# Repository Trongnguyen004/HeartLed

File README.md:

### HeartLed chưa được hoàn thiện 100% vì còn vướng về khâu tiết kiệm năng lượng vì sử dụng các pin CR2032, LIR2032, các loại pin có kích thước nhỏ mới phù hợp để làm 1 chiếc móc khóa.
### Vì giới hạn về mặt kiến thức lập trình nên hiện tại chưa thể can thiệp sâu vào các chế độ ngủ của chip. Vậy nên vấn đề trên sẽ được cải thiện dần trong thời gian tới.

### #Design 
<p align="center">
  <table>
    <tr>
      <td>
        
      </td>
      <td>
        
      </td>
      <td>
        
      </td>
    </tr>
  </table>
</p>

### #3D View
<p align="center">
  <table>
    <tr>
      <td>
        
      </td>
      <td>
        
      </td>
      <td>
        
      </td>
    </tr>
  </table>
</p>

### #Thành phẩm 
<p align="center">
  <table>
    <tr>
      <td>
        
      </td>
      <td>
        
      </td>
      <td>
        
      </td>
    </tr>
  </table>
</p>

### #Video
https://github.com/Trongnguyen004/HeartLed/assets/137270832/59e95ee1-c4d1-4318-9db8-90237cea7051

https://github.com/Trongnguyen004/HeartLed/assets/137270832/5ad59888-f046-4cde-adbe-0e13fbfc24e3

https://github.com/Trongnguyen004/HeartLed/assets/137270832/b6c706a9-fdab-4b93-9083-bb33e0925c82

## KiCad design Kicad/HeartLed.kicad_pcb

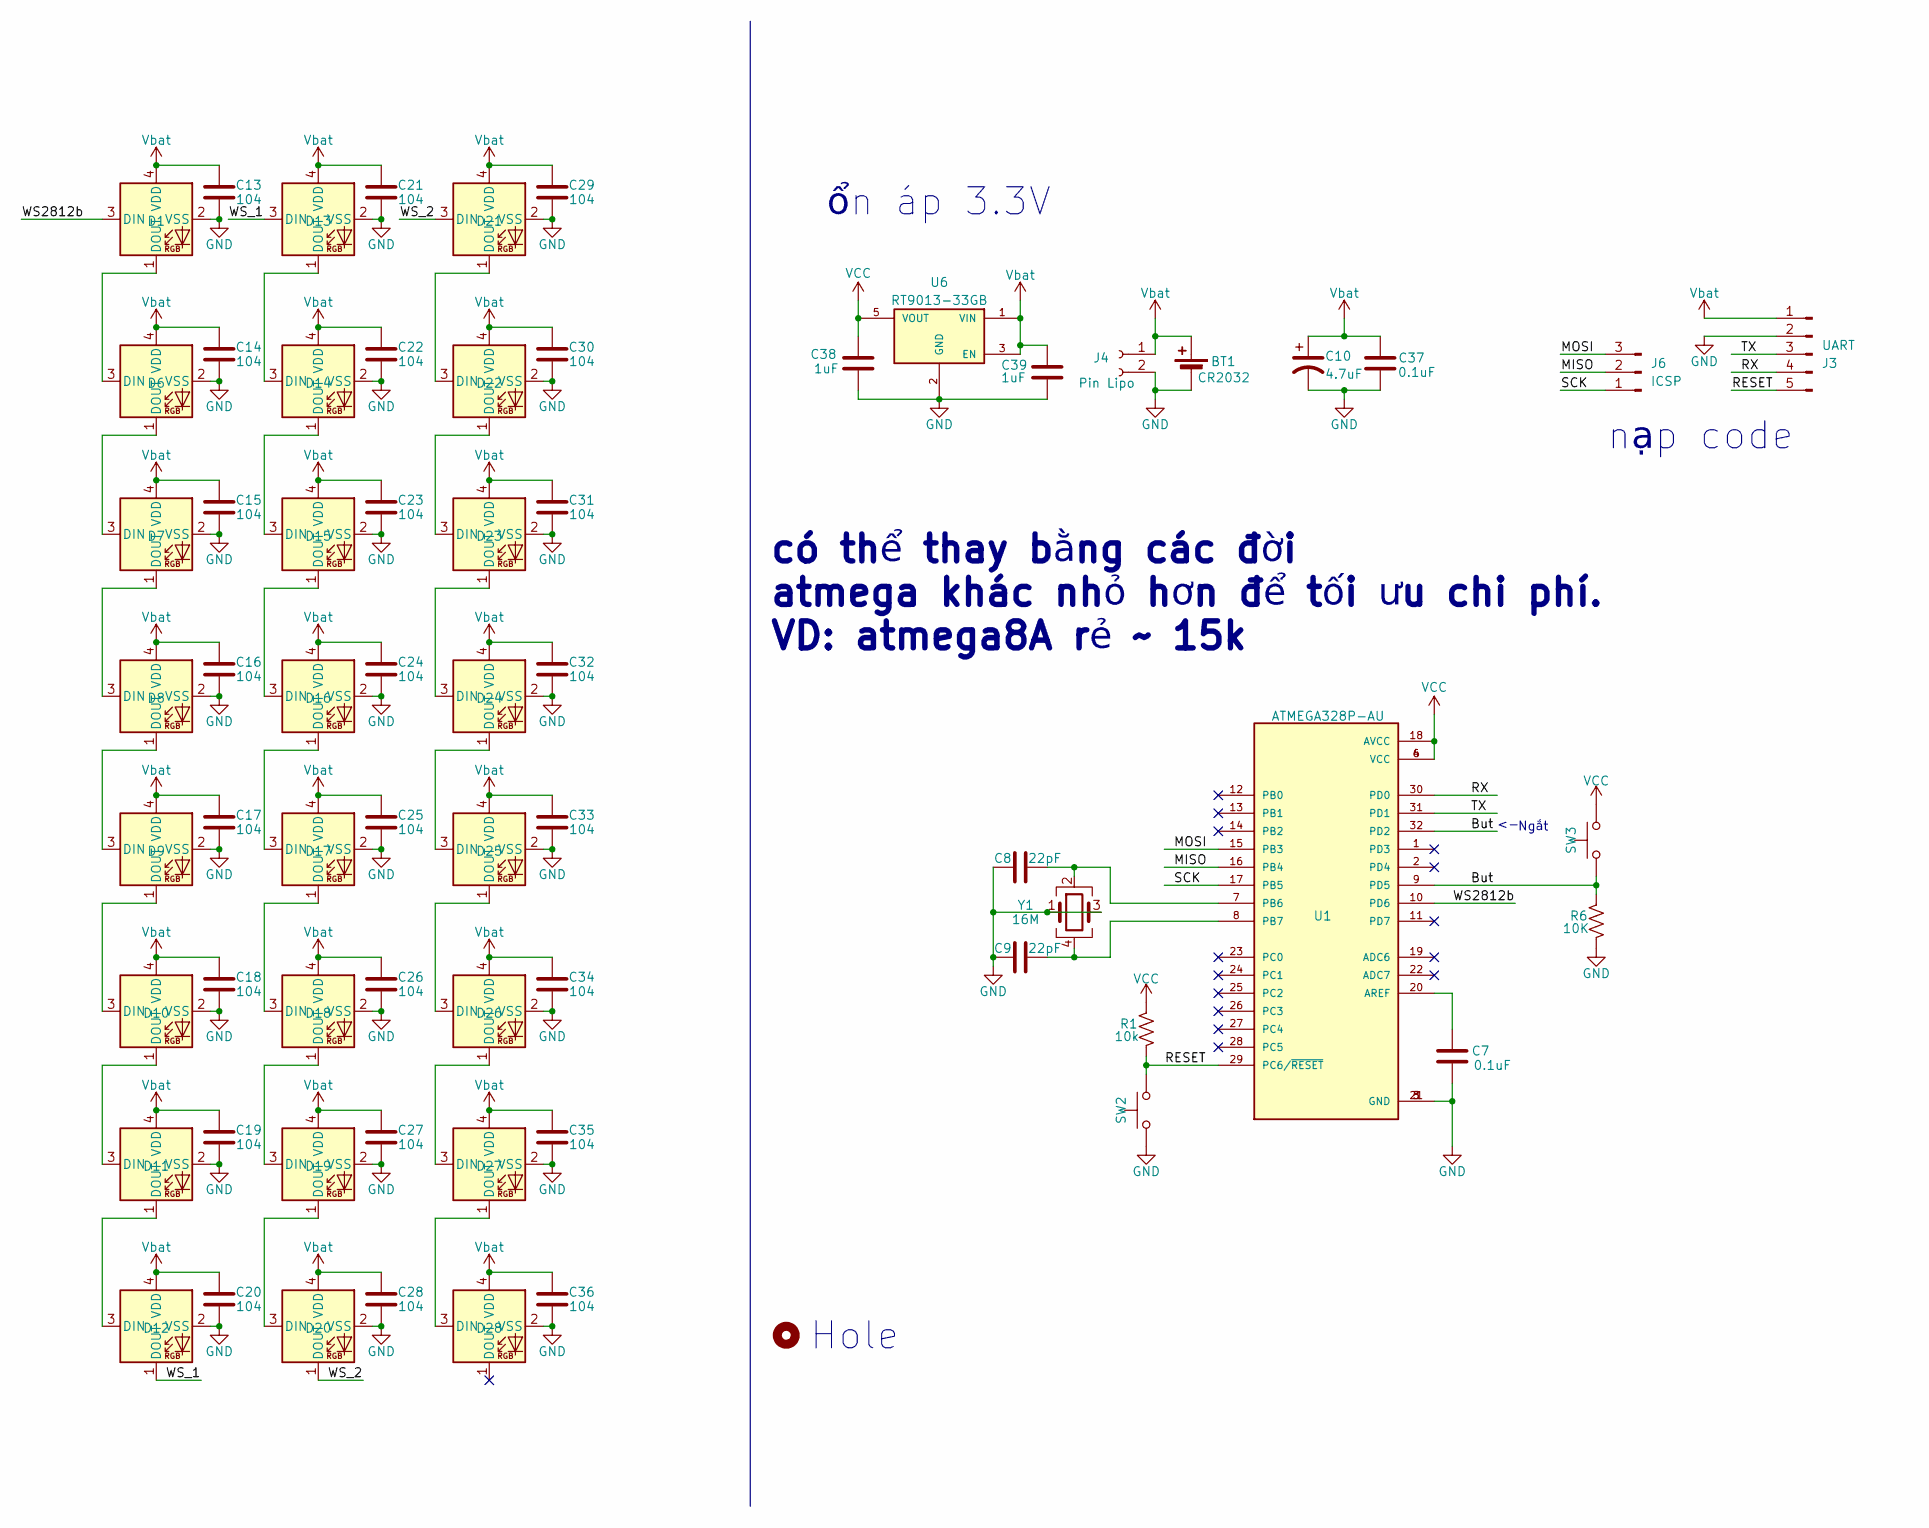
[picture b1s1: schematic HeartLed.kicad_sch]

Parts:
BT1: CR2032; BatteryHolder_MPD_BC2003_1x2032
C7, C37: 0.1uF; C_0603_1608Metric
C8, C9: 22pF; C_0805_2012Metric
C10: 4.7uF; CP_EIA-3216-18_Kemet-A_Pad1.58x1.35mm_HandSolder
C13, C14, C15, C16, C17, C18, C19, C20, C21, C22, C23, C24, C25, C26, C27, C28, C29, C30, C31, C32, C33, C34, C35, C36: 104; C_0603_1608Metric
C38, C39: 1uF; C_0805_2012Metric
D1, D6, D7, D8, D9, D10, D11, D12, D13, D14, D15, D16, D17, D18, D19, D20, D21, D22, D23, D24, D25, D26, D27, D28: WS2812B-2020; LED_WS2812B-2020_PLCC4_2.0x2.0mm
H1: HOLE; MountingHole_3.2mm_M3
J3: UART; PinHeader_1x05_P2.54mm_Vertical
J4: Pin Lipo; JST_B2B-XH-A_LF__SN_
J6: ICSP; PinHeader_1x03_P2.54mm_Vertical
R1: 10k; R_0603_1608Metric
R6: 10K; R_0603_1608Metric
SW2: RESET; SW_SPST_B3U-1000P
SW3: MODE; SW_Tactile_SPST_NO_Straight_CK_PTS636Sx25SMTRLFS
U1: ATMEGA328P-AU; QFP80P900X900X120-32N; PARTREV 8271A
U6: RT9013-33GB; SOT94P279X129-5N; PARTREV Aprill 2011
Y1: 16M; Crystal_SMD_3225-4Pin_3.2x2.5mm

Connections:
/But: R6.2, SW3.1, U1.9 (PD5), U1.32 (PD2)
/MISO: J6.2, U1.16 (PB4)
/MOSI: J6.3, U1.15 (PB3)
/RESET: J3.5, R1.1, SW2.2, U1.29 (PC6/~RESET)
/RX: J3.4, U1.30 (PD0)
/SCK: J6.1, U1.17 (PB5)
/TX: J3.3, U1.31 (PD1)
/WS2812b: D1.3 (DIN), U1.10 (PD6)
/WS_1: D12.1 (DOUT), D13.3 (DIN)
/WS_2: D20.1 (DOUT), D21.3 (DIN)
GND: BT1.2 (-), C7.1, C8.2, C9.2, C10.2, C13.1, C14.1, C15.1, C16.1, C17.1, C18.1, C19.1, C20.1, C21.1, C22.1, C23.1, C24.1, C25.1, C26.1, C27.1, C28.1, C29.1, C30.1, C31.1, C32.1, C33.1, C34.1, C35.1, C36.1, C37.1, C38.1, C39.1, D1.2 (VSS), D6.2 (VSS), D7.2 (VSS), D8.2 (VSS), D9.2 (VSS), D10.2 (VSS), D11.2 (VSS), D12.2 (VSS), D13.2 (VSS), D14.2 (VSS), D15.2 (VSS), D16.2 (VSS), D17.2 (VSS), D18.2 (VSS), D19.2 (VSS), D20.2 (VSS), D21.2 (VSS), D22.2 (VSS), D23.2 (VSS), D24.2 (VSS), D25.2 (VSS), D26.2 (VSS), D27.2 (VSS), D28.2 (VSS), J3.2, J4.2, R6.1, SW2.1, U1.3 (GND), U1.5 (GND), U1.21 (GND), U6.2 (GND), Y1.1, Y1.3
unnamed: D1.1 (DOUT), D6.3 (DIN)
unnamed: D6.1 (DOUT), D7.3 (DIN)
unnamed: D7.1 (DOUT), D8.3 (DIN)
unnamed: D8.1 (DOUT), D9.3 (DIN)
unnamed: D9.1 (DOUT), D10.3 (DIN)
unnamed: D10.1 (DOUT), D11.3 (DIN)
unnamed: D11.1 (DOUT), D12.3 (DIN)
unnamed: D13.1 (DOUT), D14.3 (DIN)
unnamed: D14.1 (DOUT), D15.3 (DIN)
unnamed: D15.1 (DOUT), D16.3 (DIN)
unnamed: D16.1 (DOUT), D17.3 (DIN)
unnamed: D17.1 (DOUT), D18.3 (DIN)
unnamed: D18.1 (DOUT), D19.3 (DIN)
unnamed: D19.1 (DOUT), D20.3 (DIN)
unnamed: D21.1 (DOUT), D22.3 (DIN)
unnamed: D22.1 (DOUT), D23.3 (DIN)
unnamed: D23.1 (DOUT), D24.3 (DIN)
unnamed: D24.1 (DOUT), D25.3 (DIN)
unnamed: D25.1 (DOUT), D26.3 (DIN)
unnamed: D26.1 (DOUT), D27.3 (DIN)
unnamed: D27.1 (DOUT), D28.3 (DIN)
unnamed: C7.2, U1.20 (AREF)
unnamed: C8.1, U1.7 (PB6), Y1.2
unnamed: C9.1, U1.8 (PB7), Y1.4
VCC: C38.2, R1.2, SW3.2, U1.4 (VCC), U1.6 (VCC), U1.18 (AVCC), U6.5 (VOUT)
Vbat: BT1.1 (+), C10.1, C13.2, C14.2, C15.2, C16.2, C17.2, C18.2, C19.2, C20.2, C21.2, C22.2, C23.2, C24.2, C25.2, C26.2, C27.2, C28.2, C29.2, C30.2, C31.2, C32.2, C33.2, C34.2, C35.2, C36.2, C37.2, C39.2, D1.4 (VDD), D6.4 (VDD), D7.4 (VDD), D8.4 (VDD), D9.4 (VDD), D10.4 (VDD), D11.4 (VDD), D12.4 (VDD), D13.4 (VDD), D14.4 (VDD), D15.4 (VDD), D16.4 (VDD), D17.4 (VDD), D18.4 (VDD), D19.4 (VDD), D20.4 (VDD), D21.4 (VDD), D22.4 (VDD), D23.4 (VDD), D24.4 (VDD), D25.4 (VDD), D26.4 (VDD), D27.4 (VDD), D28.4 (VDD), J3.1, J4.1, U6.1 (VIN), U6.3 (EN)

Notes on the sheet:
Hole
Ngắt
nạp code
có thể thay bằng các đời atmega khác nhỏ hơn để tối ưu chi phí. VD: atmega8A rẻ ~ 15k
ổn áp 3.3V

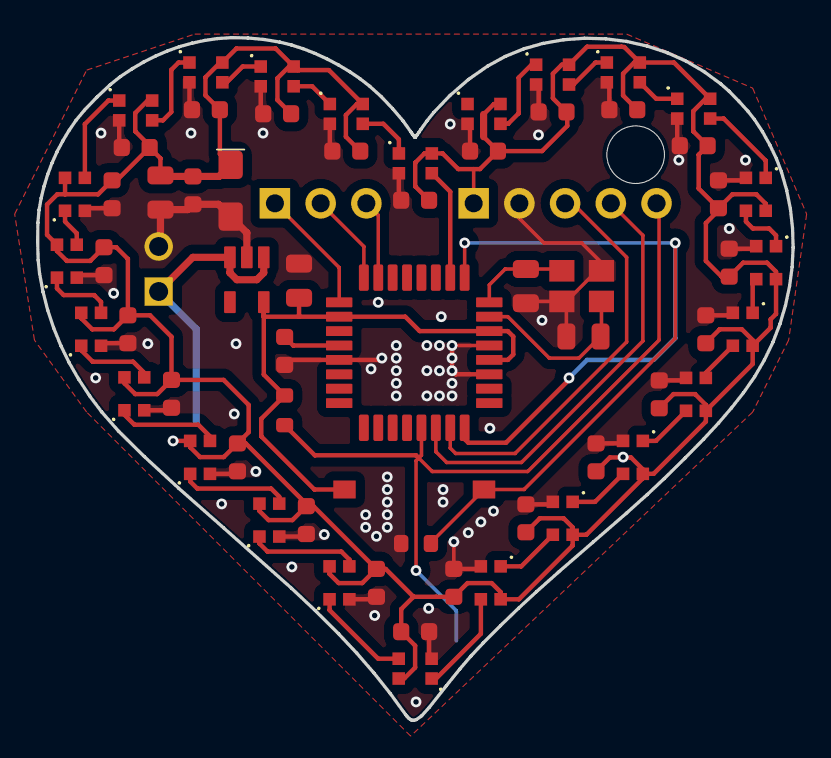
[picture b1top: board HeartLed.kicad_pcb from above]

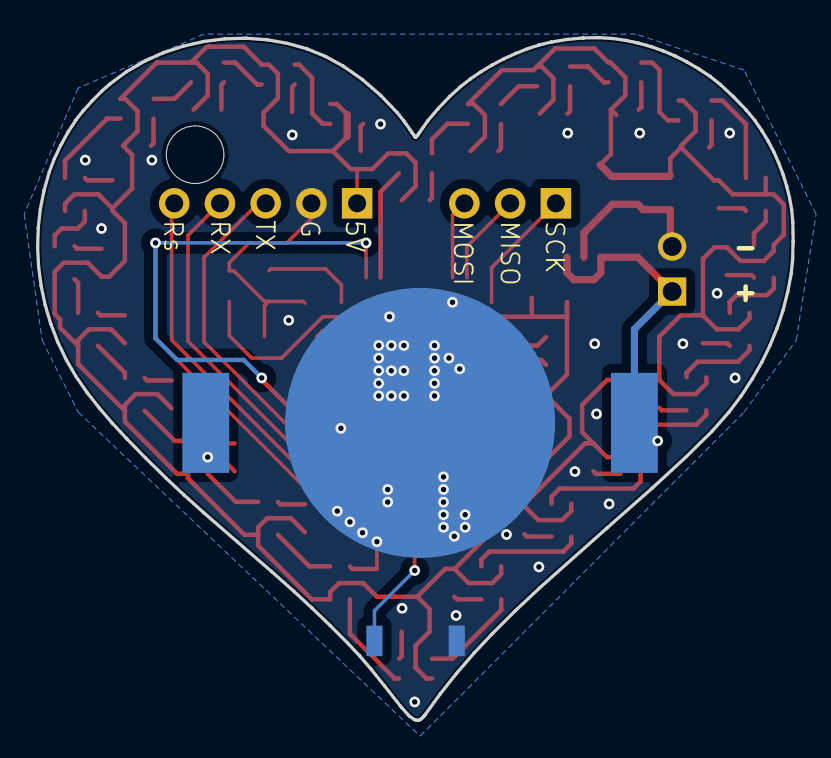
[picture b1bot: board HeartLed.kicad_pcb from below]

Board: 2 copper layers, 42.0 x 37.9 mm, 67 parts (3 on the bottom side), 37 nets.
